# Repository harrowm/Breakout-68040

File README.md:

# Breakout-68040
A breakout board for the 68LC040

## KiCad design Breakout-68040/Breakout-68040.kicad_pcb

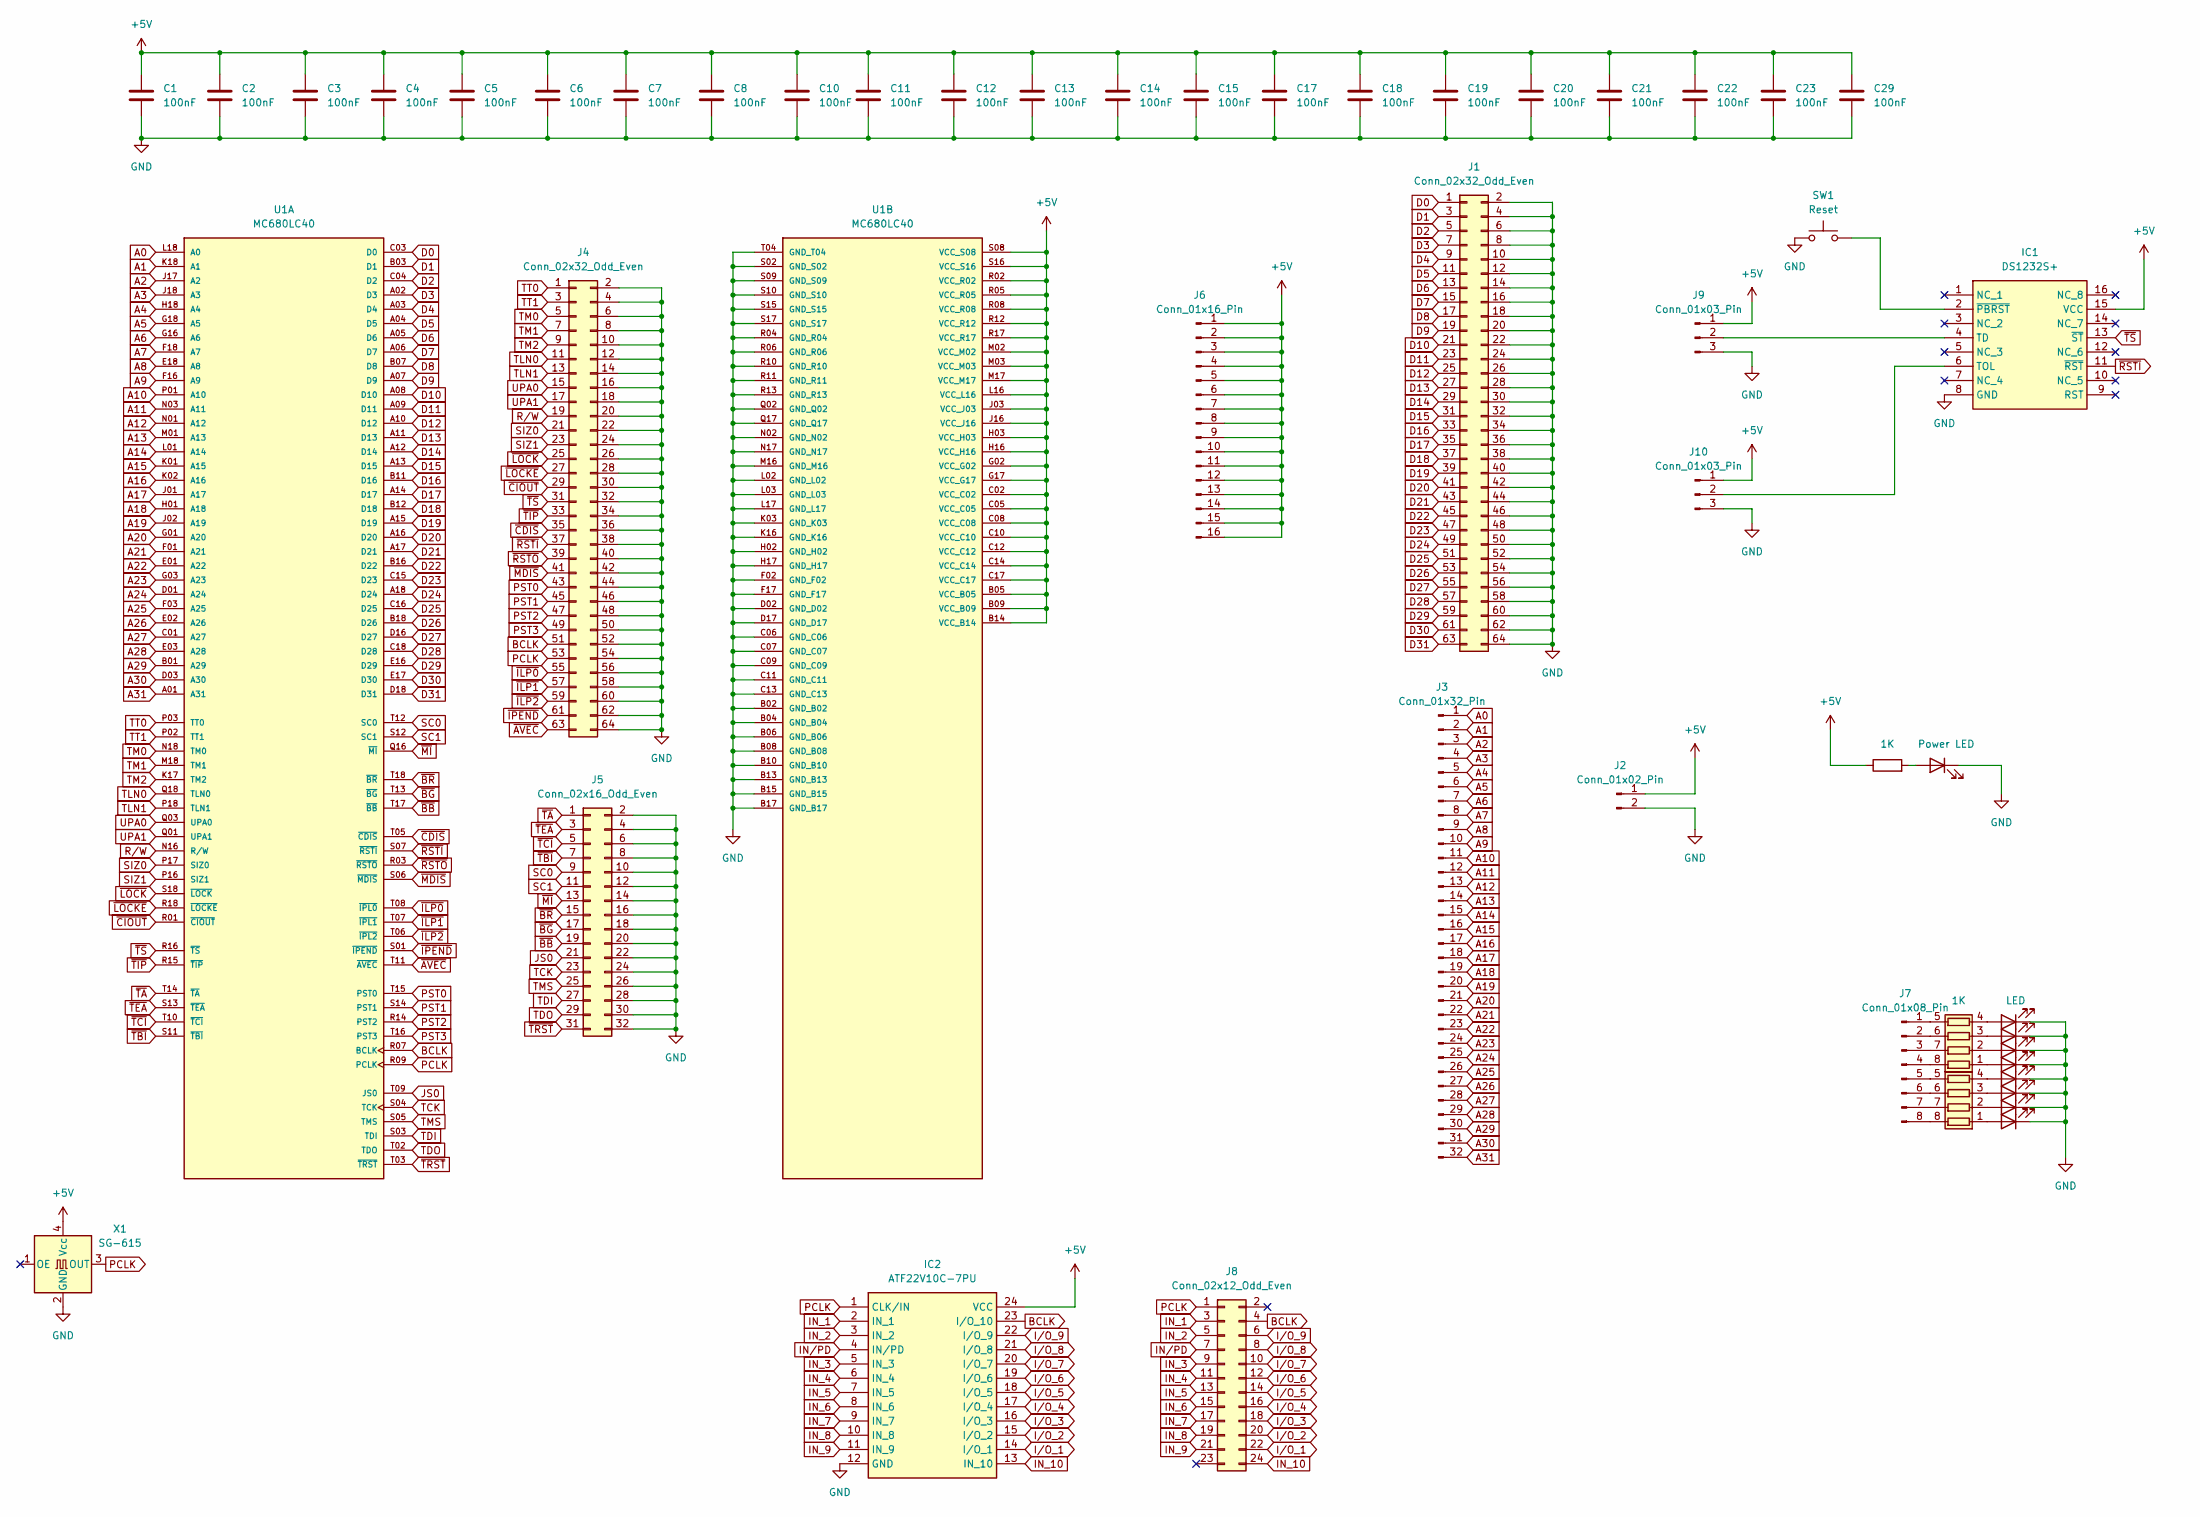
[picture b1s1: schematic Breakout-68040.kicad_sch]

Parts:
C1, C2, C3, C4, C5, C6, C7, C8, C10, C11, C12, C13, C14, C15, C17, C18, C19, C20, C21, C22, C23, C29: 100nF; C_0805_2012Metric_Pad1.18x1.45mm_HandSolder; JLC 0805
D1: Power LED; LED_0805_2012Metric_Pad1.15x1.40mm_HandSolder; LCSC C2297
D19, D20, D21, D22, D23, D24, D25, D26: LED; LED_0805_2012Metric_Pad1.15x1.40mm_HandSolder; JLC 805
IC1: DS1232S+; SOIC-16W_7.5x10.3mm_P1.27mm; Mouser Part Number 700-DS1232S
IC2: ATF22V10C-7PU; DIP-24_W7.62mm_LongPads; Mouser Part Number 556-AF22V10C15PU
J1, J4: Conn_02x32_Odd_Even; PinHeader_2x32_P2.54mm_Vertical
J2: Conn_01x02_Pin; PinHeader_1x02_P2.54mm_Vertical
J3: Conn_01x32_Pin; PinHeader_1x32_P2.54mm_Vertical
J5: Conn_02x16_Odd_Even; PinHeader_2x16_P2.54mm_Vertical
J6: Conn_01x16_Pin; PinHeader_1x16_P2.54mm_Vertical
J7: Conn_01x08_Pin; PinHeader_1x08_P2.54mm_Vertical
J8: Conn_02x12_Odd_Even; PinHeader_2x12_P2.54mm_Vertical
J9, J10: Conn_01x03_Pin; PinHeader_1x03_P2.54mm_Vertical
R1: 1K; R_0805_2012Metric_Pad1.20x1.40mm_HandSolder; JLC 805
RN1: 1K; R_Array_Convex_4x0603; JLC 0603x4
RN2: R_Pack04; R_Array_Convex_4x0603; JLC 0603x4
SW1: Reset; SW_TH_Tactile_Omron_B3F-10xx
U1: MC680LC40; PGA179_BIG
X1: SG-615; Oscillator_SMD_SeikoEpson_SG8002JA-4Pin_14.0x8.7mm

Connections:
+5V: C1.1, C2.1, C3.1, C4.1, C5.1, C6.1, C7.1, C8.1, C10.1, C11.1, C12.1, C13.1, C14.1, C15.1, C17.1, C18.1, C19.1, C20.1, C21.1, C22.1, C23.1, C29.1, IC1.15 (VCC), IC2.24 (VCC), J2.1, J6.1, J6.2, J6.3, J6.4, J6.5, J6.6, J6.7, J6.8, J6.9, J6.10, J6.11, J6.12, J6.13, J6.14, J6.15, J6.16, J9.1, J10.1, R1.1, U1.B05 (VCC_B05), U1.B09 (VCC_B09), U1.B14 (VCC_B14), U1.C02 (VCC_C02), U1.C05 (VCC_C05), U1.C08 (VCC_C08), U1.C10 (VCC_C10), U1.C12 (VCC_C12), U1.C14 (VCC_C14), U1.C17 (VCC_C17), U1.G02 (VCC_G02), U1.G17 (VCC_G17), U1.H03 (VCC_H03), U1.H16 (VCC_H16), U1.J03 (VCC_J03), U1.J16 (VCC_J16), U1.L16 (VCC_L16), U1.M02 (VCC_M02), U1.M03 (VCC_M03), U1.M17 (VCC_M17), U1.R02 (VCC_R02), U1.R05 (VCC_R05), U1.R08 (VCC_R08), U1.R12 (VCC_R12), U1.R17 (VCC_R17), U1.S08 (VCC_S08), U1.S16 (VCC_S16), X1.4 (Vcc)
A0: J3.1, U1.L18 (A0)
A1: J3.2, U1.K18 (A1)
A2: J3.3, U1.J17 (A2)
A3: J3.4, U1.J18 (A3)
A4: J3.5, U1.H18 (A4)
A5: J3.6, U1.G18 (A5)
A6: J3.7, U1.G16 (A6)
A7: J3.8, U1.F18 (A7)
A8: J3.9, U1.E18 (A8)
A9: J3.10, U1.F16 (A9)
A10: J3.11, U1.P01 (A10)
A11: J3.12, U1.N03 (A11)
A12: J3.13, U1.N01 (A12)
A13: J3.14, U1.M01 (A13)
A14: J3.15, U1.L01 (A14)
A15: J3.16, U1.K01 (A15)
A16: J3.17, U1.K02 (A16)
A17: J3.18, U1.J01 (A17)
A18: J3.19, U1.H01 (A18)
A19: J3.20, U1.J02 (A19)
A20: J3.21, U1.G01 (A20)
A21: J3.22, U1.F01 (A21)
A22: J3.23, U1.E01 (A22)
A23: J3.24, U1.G03 (A23)
A24: J3.25, U1.D01 (A24)
A25: J3.26, U1.F03 (A25)
A26: J3.27, U1.E02 (A26)
A27: J3.28, U1.C01 (A27)
A28: J3.29, U1.E03 (A28)
A29: J3.30, U1.B01 (A29)
A30: J3.31, U1.D03 (A30)
A31: J3.32, U1.A01 (A31)
BCLK: IC2.23 (I/O_10), J4.51, J8.4, U1.R07 (BCLK)
D0: J1.1, U1.C03 (D0)
D1: J1.3, U1.B03 (D1)
D2: J1.5, U1.C04 (D2)
D3: J1.7, U1.A02 (D3)
D4: J1.9, U1.A03 (D4)
D5: J1.11, U1.A04 (D5)
D6: J1.13, U1.A05 (D6)
D7: J1.15, U1.A06 (D7)
D8: J1.17, U1.B07 (D8)
D9: J1.19, U1.A07 (D9)
D10: J1.21, U1.A08 (D10)
D11: J1.23, U1.A09 (D11)
D12: J1.25, U1.A10 (D12)
D13: J1.27, U1.A11 (D13)
D14: J1.29, U1.A12 (D14)
D15: J1.31, U1.A13 (D15)
D16: J1.33, U1.B11 (D16)
D17: J1.35, U1.A14 (D17)
D18: J1.37, U1.B12 (D18)
D19: J1.39, U1.A15 (D19)
D20: J1.41, U1.A16 (D20)
D21: J1.43, U1.A17 (D21)
D22: J1.45, U1.B16 (D22)
D23: J1.47, U1.C15 (D23)
D24: J1.49, U1.A18 (D24)
D25: J1.51, U1.C16 (D25)
D26: J1.53, U1.B18 (D26)
D27: J1.55, U1.D16 (D27)
D28: J1.57, U1.C18 (D28)
D29: J1.59, U1.E16 (D29)
D30: J1.61, U1.E17 (D30)
D31: J1.63, U1.D18 (D31)
GND: C1.2, C2.2, C3.2, C4.2, C5.2, C6.2, C7.2, C8.2, C10.2, C11.2, C12.2, C13.2, C14.2, C15.2, C17.2, C18.2, C19.2, C20.2, C21.2, C22.2, C23.2, C29.2, D1.1 (K), D19.1 (K), D20.1 (K), D21.1 (K), D22.1 (K), D23.1 (K), D24.1 (K), D25.1 (K), D26.1 (K), IC1.8 (GND), IC2.12 (GND), J1.2, J1.4, J1.6, J1.8, J1.10, J1.12, J1.14, J1.16, J1.18, J1.20, J1.22, J1.24, J1.26, J1.28, J1.30, J1.32, J1.34, J1.36, J1.38, J1.40, J1.42, J1.44, J1.46, J1.48, J1.50, J1.52, J1.54, J1.56, J1.58, J1.60, J1.62, J1.64, J2.2, J4.2, J4.4, J4.6, J4.8, J4.10, J4.12, J4.14, J4.16, J4.18, J4.20, J4.22, J4.24, J4.26, J4.28, J4.30, J4.32, J4.34, J4.36, J4.38, J4.40, J4.42, J4.44, J4.46, J4.48, J4.50, J4.52, J4.54, J4.56, J4.58, J4.60, J4.62, J4.64, J5.2, J5.4, J5.6, J5.8, J5.10, J5.12, J5.14, J5.16, J5.18, J5.20, J5.22, J5.24, J5.26, J5.28, J5.30, J5.32, J9.3, J10.3, SW1.1, U1.B02 (GND_B02), U1.B04 (GND_B04), U1.B06 (GND_B06), U1.B08 (GND_B08), U1.B10 (GND_B10), U1.B13 (GND_B13), U1.B15 (GND_B15), U1.B17 (GND_B17), U1.C06 (GND_C06), U1.C07 (GND_C07), U1.C09 (GND_C09), U1.C11 (GND_C11), U1.C13 (GND_C13), U1.D02 (GND_D02), U1.D17 (GND_D17), U1.F02 (GND_F02), U1.F17 (GND_F17), U1.H02 (GND_H02), U1.H17 (GND_H17), U1.K03 (GND_K03), U1.K16 (GND_K16), U1.L02 (GND_L02), U1.L03 (GND_L03), U1.L17 (GND_L17), U1.M16 (GND_M16), U1.N02 (GND_N02), U1.N17 (GND_N17), U1.Q02 (GND_Q02), U1.Q17 (GND_Q17), U1.R04 (GND_R04), U1.R06 (GND_R06), U1.R10 (GND_R10), U1.R11 (GND_R11), U1.R13 (GND_R13), U1.S02 (GND_S02), U1.S09 (GND_S09), U1.S10 (GND_S10), U1.S15 (GND_S15), U1.S17 (GND_S17), U1.T04 (GND_T04), X1.2 (GND)
IN_1: IC2.2 (IN_1), J8.3
IN_2: IC2.3 (IN_2), J8.5
IN_3: IC2.5 (IN_3), J8.9
IN_4: IC2.6 (IN_4), J8.11
IN_5: IC2.7 (IN_5), J8.13
IN_6: IC2.8 (IN_6), J8.15
IN_7: IC2.9 (IN_7), J8.17
IN_8: IC2.10 (IN_8), J8.19
IN_9: IC2.11 (IN_9), J8.21
IN_10: IC2.13 (IN_10), J8.24
IN/PD: IC2.4 (IN/PD), J8.7
I/O_1: IC2.14 (I/O_1), J8.22
I/O_2: IC2.15 (I/O_2), J8.20
I/O_3: IC2.16 (I/O_3), J8.18
I/O_4: IC2.17 (I/O_4), J8.16
I/O_5: IC2.18 (I/O_5), J8.14
I/O_6: IC2.19 (I/O_6), J8.12
I/O_7: IC2.20 (I/O_7), J8.10
I/O_8: IC2.21 (I/O_8), J8.8
I/O_9: IC2.22 (I/O_9), J8.6
JS0: J5.21, U1.T09 (JS0)
unnamed: D1.2 (A), R1.2
unnamed: D19.2 (A), RN1.4 (R4.1)
unnamed: D20.2 (A), RN1.3 (R3.1)
unnamed: D21.2 (A), RN1.2 (R2.1)
unnamed: D22.2 (A), RN1.1 (R1.1)
unnamed: D23.2 (A), RN2.4 (R4.1)
unnamed: D24.2 (A), RN2.3 (R3.1)
unnamed: D25.2 (A), RN2.2 (R2.1)
unnamed: D26.2 (A), RN2.1 (R1.1)
unnamed: IC1.4 (TD), J9.2
unnamed: IC1.6 (TOL), J10.2
unnamed: IC1.2 (~PBRST), SW1.2
unnamed: J7.1, RN1.5 (R4.2)
unnamed: J7.2, RN1.6 (R3.2)
unnamed: J7.3, RN1.7 (R2.2)
unnamed: J7.4, RN1.8 (R1.2)
unnamed: J7.5, RN2.5 (R4.2)
unnamed: J7.6, RN2.6 (R3.2)
unnamed: J7.7, RN2.7 (R2.2)
unnamed: J7.8, RN2.8 (R1.2)
PCLK: IC2.1 (CLK/IN), J4.53, J8.1, U1.R09 (PCLK), X1.3 (OUT)
PST0: J4.43, U1.T15 (PST0)
PST1: J4.45, U1.S14 (PST1)
PST2: J4.47, U1.R14 (PST2)
PST3: J4.49, U1.T16 (PST3)
R/W: J4.19, U1.N16 (R/W)
SC0: J5.9, U1.T12 (SC0)
SC1: J5.11, U1.S12 (SC1)
SIZ0: J4.21, U1.P17 (SIZ0)
SIZ1: J4.23, U1.P16 (SIZ1)
TCK: J5.23, U1.S04 (TCK)
TDI: J5.27, U1.S03 (TDI)
TDO: J5.29, U1.T02 (TDO)
TLN0: J4.11, U1.Q18 (TLN0)
TLN1: J4.13, U1.P18 (TLN1)
TM0: J4.5, U1.N18 (TM0)
TM1: J4.7, U1.M18 (TM1)
TM2: J4.9, U1.K17 (TM2)
TMS: J5.25, U1.S05 (TMS)
TT0: J4.1, U1.P03 (TT0)
TT1: J4.3, U1.P02 (TT1)
UPA0: J4.15, U1.Q03 (UPA0)
UPA1: J4.17, U1.Q01 (UPA1)
~AVEC: J4.63, U1.T11 (~AVEC)
~BB: J5.19, U1.T17 (~BB)
~BG: J5.17, U1.T13 (~BG)
~BR: J5.15, U1.T18 (~BR)
~CDIS: J4.35, U1.T05 (~CDIS)
~CIOUT: J4.29, U1.R01 (~CIOUT)
~ILP0: J4.55, U1.T08 (~IPL0)
~ILP1: J4.57, U1.T07 (~IPL1)
~ILP2: J4.59, U1.T06 (~IPL2)
~IPEND: J4.61, U1.S01 (~IPEND)
~LOCKE: J4.27, U1.R18 (~LOCKE)
~LOCK: J4.25, U1.S18 (~LOCK)
~MDIS: J4.41, U1.S06 (~MDIS)
~MI: J5.13, U1.Q16 (~MI)
~RSTI: IC1.11 (~RST), J4.37, U1.S07 (~RSTI)
~RSTO: J4.39, U1.R03 (~RSTO)
~TA: J5.1, U1.T14 (~TA)
~TBI: J5.7, U1.S11 (~TBI)
~TCI: J5.5, U1.T10 (~TCI)
~TEA: J5.3, U1.S13 (~TEA)
~TIP: J4.33, U1.R15 (~TIP)
~TRST: J5.31, U1.T03 (~TRST)
~TS: IC1.13 (~ST), J4.31, U1.R16 (~TS)

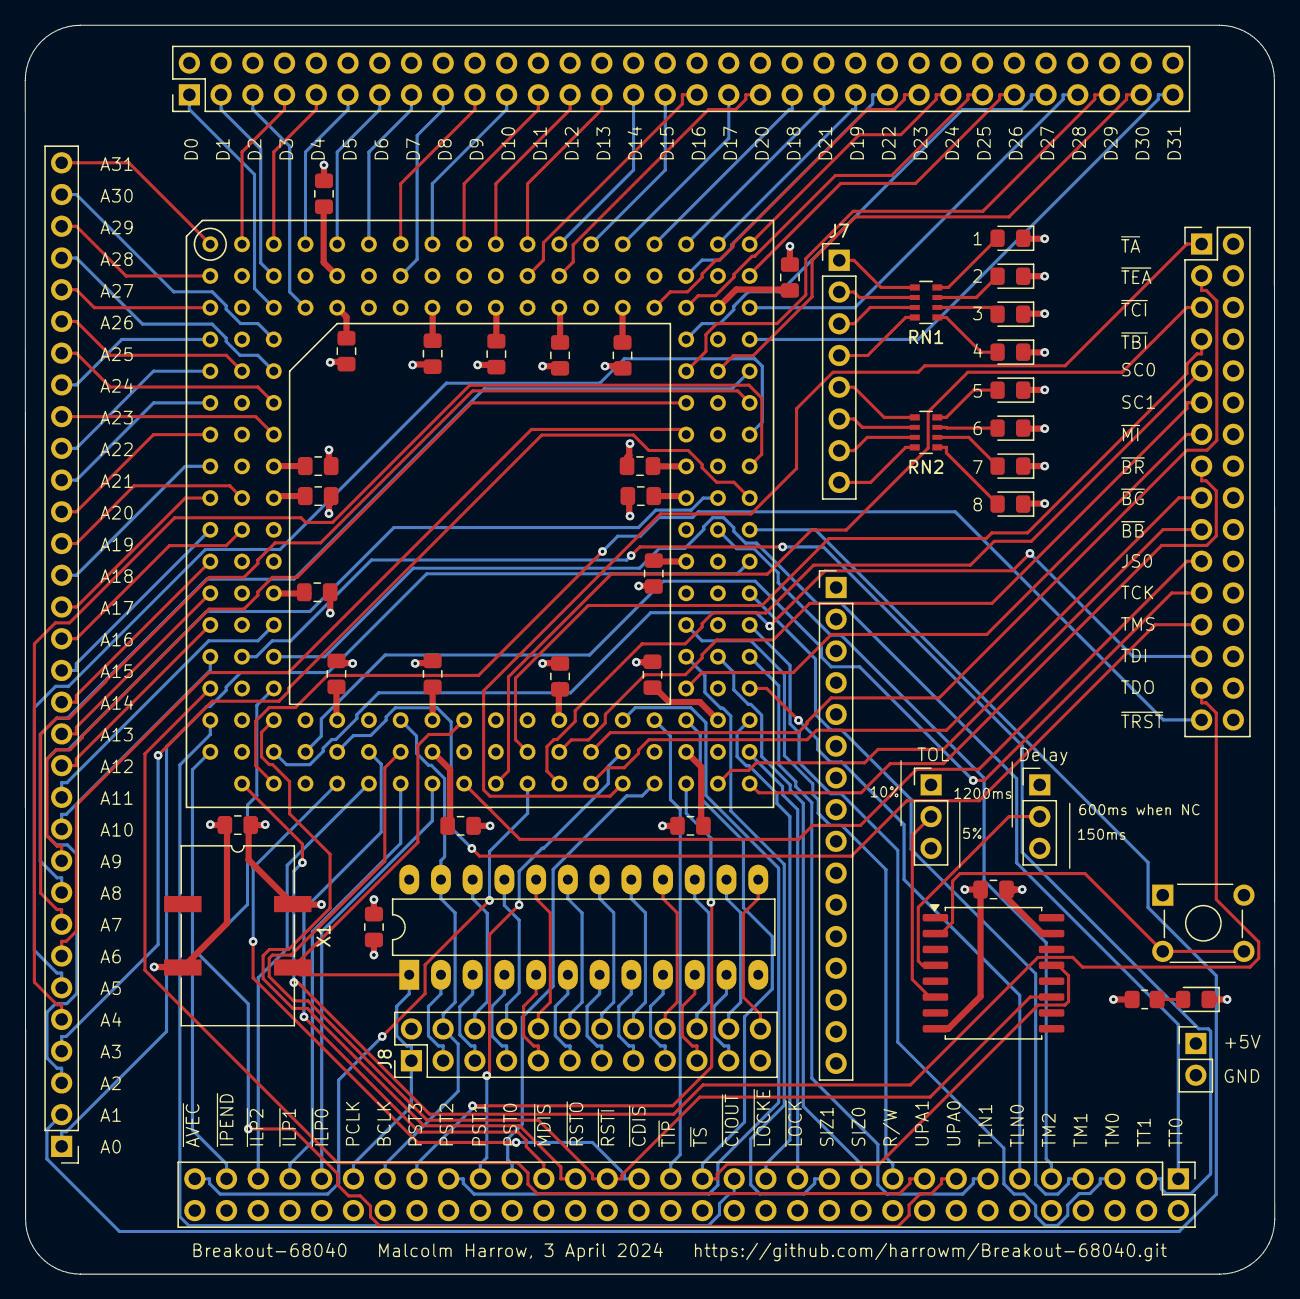
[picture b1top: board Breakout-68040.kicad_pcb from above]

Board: 4 copper layers, 100.0 x 100.0 mm, 49 parts (0 on the bottom side), 154 nets.

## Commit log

2024-04-04 First routed version
2024-04-04 JLCPCB manufacturing info
2024-04-04 Sent to jclpcb
2025-03-14 Mothballing
